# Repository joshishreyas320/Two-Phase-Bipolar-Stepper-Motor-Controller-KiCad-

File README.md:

# Two Phase Bipolar Stepper Motor Controller

> KiCad PCB Design | 2-Layer Board | L297 + L298N Driver

---

## Project Description
A 2-phase bipolar stepper motor controller PCB designed using **KiCad**. The board uses the **L297 stepper sequencer IC** and **L298N dual H-bridge driver** to provide full-bridge drive for a 2-phase bipolar stepper motor. Supports STEP/DIR input from any MCU, with flyback diode protection and screw terminal connectors for motor and power wiring.

**Short Description (≤350 chars):**
> 2-phase bipolar stepper motor driver PCB using L297+L298N ICs. Supports STEP/DIR input, full-bridge drive up to 2A/channel, with flyback diode protection. Designed in KiCad with Gerber output.

---

## Key Components

| Component | Description |
|-----------|-------------|
| **L297** | Stepper motor controller IC – generates phase sequences from STEP/DIR |
| **L298N** | Dual full-bridge driver – up to 46V, 2A per channel (4A peak) |
| **Schottky Diodes (8x)** | Flyback protection for H-bridge inductive switching |
| **Screw Terminals (J1–J4)** | Motor coil and power supply connections |
| **Capacitors** | Power decoupling and filtering |
| **Current Sense Resistors** | Motor current feedback to L297 |

---

## Design Features
- Full-bridge bipolar drive for both stepper motor windings
- L297 auto-generates A/B/C/D phase winding sequences from STEP/DIR
- L298N handles high current switching up to 2A/channel continuously
- 8x Schottky flyback diodes protect driver from inductive voltage spikes
- Screw terminal blocks for easy motor and power wiring
- Complete Gerber files generated for PCB fabrication

---

## Signal Flow
```
MCU / Signal Source
       ↓
  STEP / DIR Inputs
       ↓
  L297 – Phase Sequencer (STEP/DIR → Phase A/B/C/D)
       ↓
  L298N – Dual H-Bridge Driver
       ↓
  Stepper Motor Coils (2-Phase Bipolar)
       ↑
  Flyback Diodes ← Inductive Kickback Protection
```

---

## Files Included
- two_phase_bipolar_stepper_motor.kicad_sch – Schematic
- two_phase_bipolar_stepper_motor.kicad_pcb – PCB Layout
- GREBBER_FILES_for_stepper_motor_controller/ – Gerber files for manufacturing
- Drill files/ – NC Drill files (PTH + NPTH)

---

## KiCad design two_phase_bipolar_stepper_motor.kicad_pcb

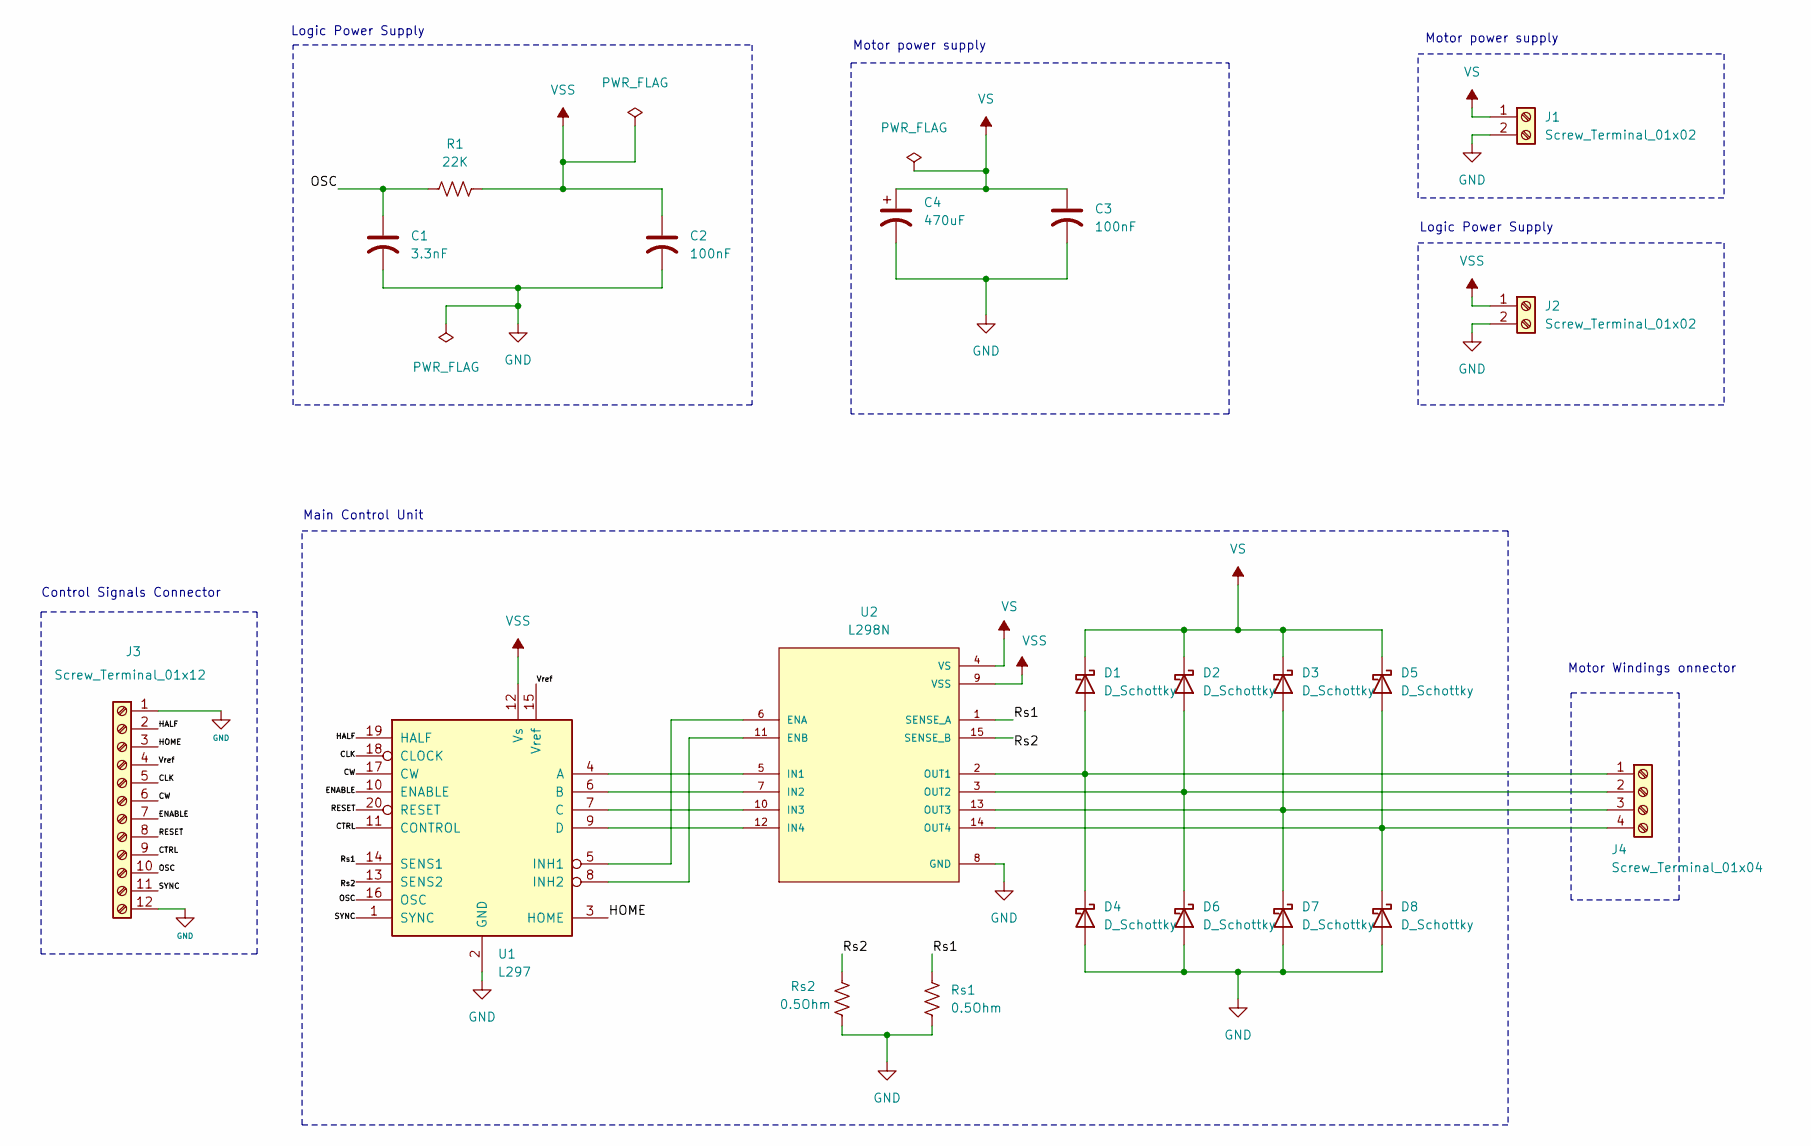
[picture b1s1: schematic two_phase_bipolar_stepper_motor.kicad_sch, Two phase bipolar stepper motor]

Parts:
C1: 3.3nF; C_Rect_L10.0mm_W3.0mm_P7.50mm_FKS3_FKP3
C2, C3: 100nF; C_Rect_L7.5mm_W6.5mm_P5.00mm
C4: 470uF; CP_Radial_D13.0mm_P7.50mm
D1, D2, D3, D4, D5, D6, D7, D8: D_Schottky; D_DO-27_P15.24mm_Horizontal
J1, J2: Screw_Terminal_01x02; TerminalBlock_Phoenix_MKDS-1,5-2-5.08_1x02_P5.08mm_Horizont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
J3: Screw_Terminal_01x12; TerminalBlock_Phoenix_MKDS-1,5-12_1x12_P5.00mm_Horizontal
J4: Screw_Terminal_01x04; TerminalBlock_Phoenix_MKDS-1,5-4_1x04_P5.00mm_Horizontal
R1: 22K; R_Axial_DIN0922_L20.0mm_D9.0mm_P25.40mm_Horizontal
Rs1, Rs2: 0.5Ohm; R_Axial_DIN0414_L11.9mm_D4.5mm_P15.24mm_Horizontal
U1: L297; CERDIP-20_W7.62mm_SideBrazed_LongPads
U2: L298N; TO127P2020X500X2100-15

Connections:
/CLK: J3.5, U1.18 (CLOCK)
/CTRL: J3.9, U1.11 (CONTROL)
/CW: J3.6, U1.17 (CW)
/ENABLE: J3.7, U1.10 (ENABLE)
/HALF: J3.2, U1.19 (HALF)
/HOME: J3.3, U1.3 (HOME)
/OSC: C1.1, J3.10, R1.1, U1.16 (OSC)
/RESET: J3.8, U1.20 (RESET)
/Rs1: Rs1.1, U1.14 (SENS1), U2.1 (SENSE_A)
/Rs2: Rs2.1, U1.13 (SENS2), U2.15 (SENSE_B)
/SYNC: J3.11, U1.1 (SYNC)
/Vref: J3.4, U1.15 (Vref)
GND: C1.2, C2.2, C3.2, C4.2, D4.2 (A), D6.2 (A), D7.2 (A), D8.2 (A), J1.2, J2.2, J3.1, J3.12, Rs1.2, Rs2.2, U1.2 (GND), U2.8 (GND)
unnamed: D1.2 (A), D4.1 (K), J4.1, U2.2 (OUT1)
unnamed: D2.2 (A), D6.1 (K), J4.2, U2.3 (OUT2)
unnamed: D3.2 (A), D7.1 (K), J4.3, U2.13 (OUT3)
unnamed: D5.2 (A), D8.1 (K), J4.4, U2.14 (OUT4)
unnamed: U1.4 (A), U2.5 (IN1)
unnamed: U1.6 (B), U2.7 (IN2)
unnamed: U1.7 (C), U2.10 (IN3)
unnamed: U1.9 (D), U2.12 (IN4)
unnamed: U1.5 (INH1), U2.6 (ENA)
unnamed: U1.8 (INH2), U2.11 (ENB)
VS: C3.1, C4.1, D1.1 (K), D2.1 (K), D3.1 (K), D5.1 (K), J1.1, U2.4 (VS)
VSS: C2.1, J2.1, R1.2, U1.12 (Vs), U2.9 (VSS)

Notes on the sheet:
Logic Power Supply
Motor power supply
Control Signals Connector
Main Control Unit
Motor Windings onnector

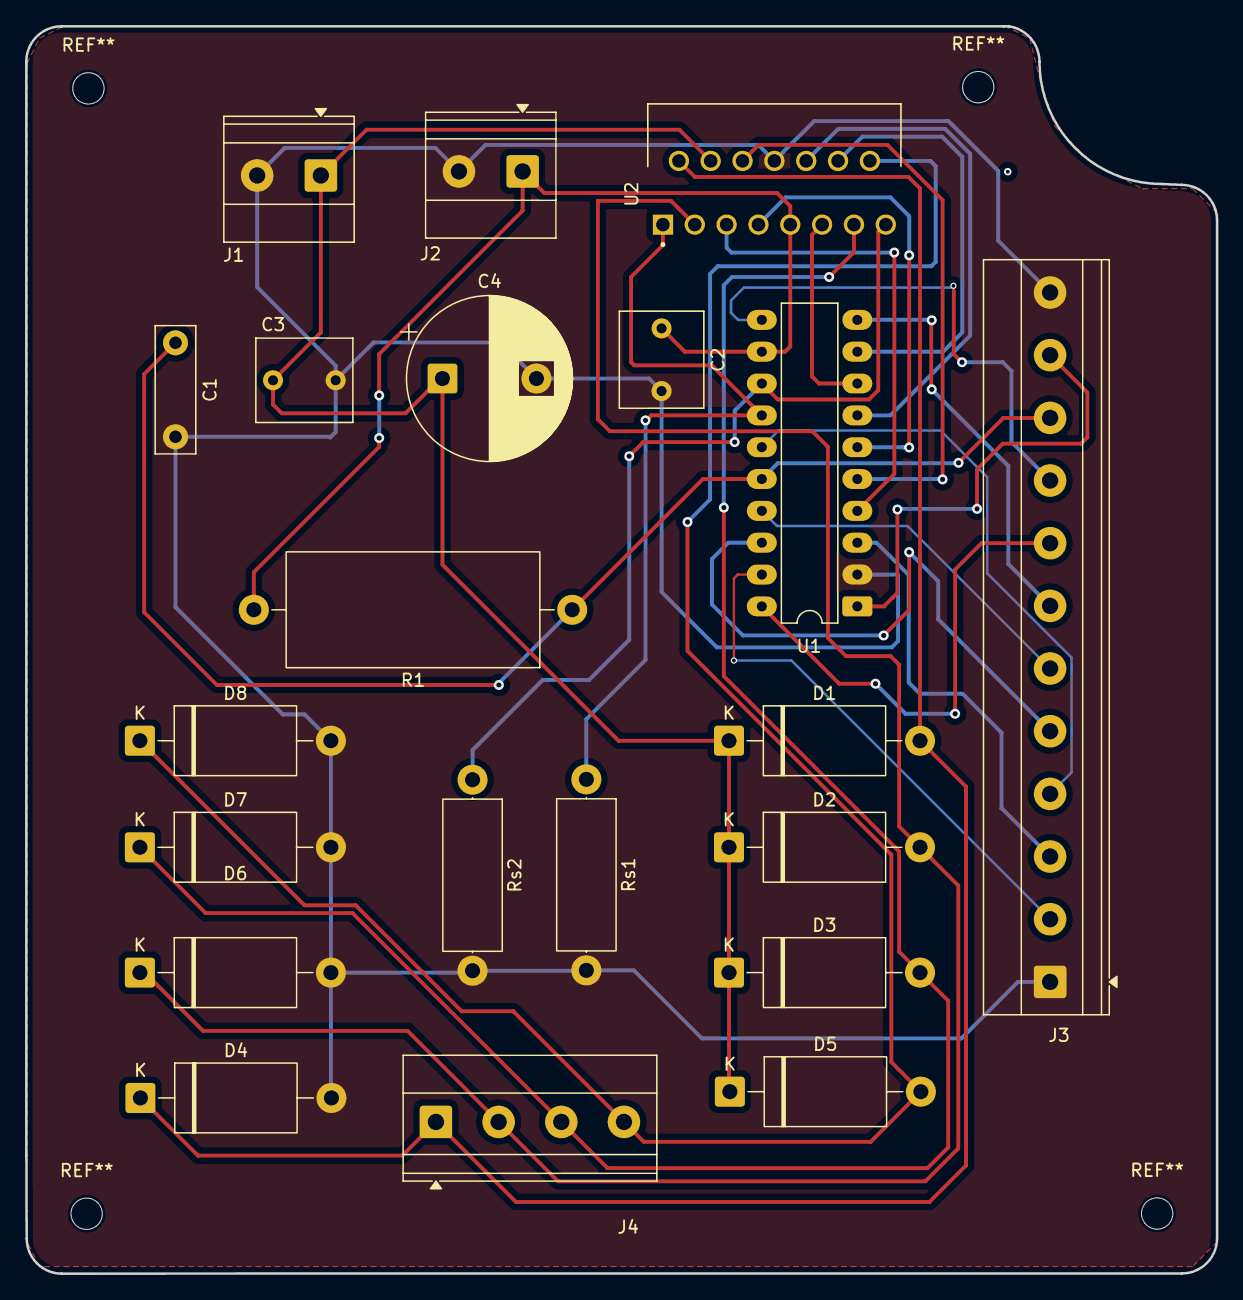
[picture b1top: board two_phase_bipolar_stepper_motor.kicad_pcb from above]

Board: 2 copper layers, 95.0 x 99.5 mm, 21 parts (0 on the bottom side), 25 nets.

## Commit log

2026-06-06 Revise README for stepper motor controller project
    Updated README to provide detailed project description, key components, design features, signal flow, and included files.
